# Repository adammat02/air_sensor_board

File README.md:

# Air Sensor Board

A low-power air sensor board (temperature and humidity) based on the Nordic **nRF54L15** SoC, designed to run as a **Matter** device.

The hardware is designed in KiCad.

## Features

- **MCU:** Nordic nRF54L15 (2.4 GHz radio, Thread / Bluetooth LE)
- **Sensor:** Sensirion SHT3x digital temperature and humidity sensor (I²C)
- **Status LED:** indicates device state (pairing, network connection, errors)
- **Button:** user input (e.g. commissioning, factory reset)
- **External flash memory:** extra storage, e.g. for OTA firmware updates (DFU)
- **Antenna:** 2.4 GHz PCB antenna
- **Power:** CR2032 coin cell battery
- **Battery monitoring:** battery voltage measured with the built-in SAADC
- **Clocks:** two external crystal oscillators
  - high-frequency crystal (HFXO, 32 MHz) for the radio and high-speed clock
  - low-frequency crystal (LFXO, 32.768 kHz) for low-power timekeeping in sleep modes

## Matter

The board is built to work in a **Matter** network, using **Thread** as the transport and **Bluetooth LE** for commissioning. It is meant to report temperature, humidity, and battery level to a Matter controller (e.g. Apple Home, Google Home, Home Assistant).

## Repository layout

| File | Description |
|------|-------------|
| `air_sensor_board.kicad_pro` | KiCad project |
| `air_sensor_board.kicad_sch` | Schematic |
| `air_sensor_board.kicad_pcb` | PCB layout |

## Tools

- [KiCad](https://www.kicad.org/) (hardware design)
- [nRF Connect SDK](https://www.nordicsemi.com/Products/Development-software/nRF-Connect-SDK) (firmware, Matter support)

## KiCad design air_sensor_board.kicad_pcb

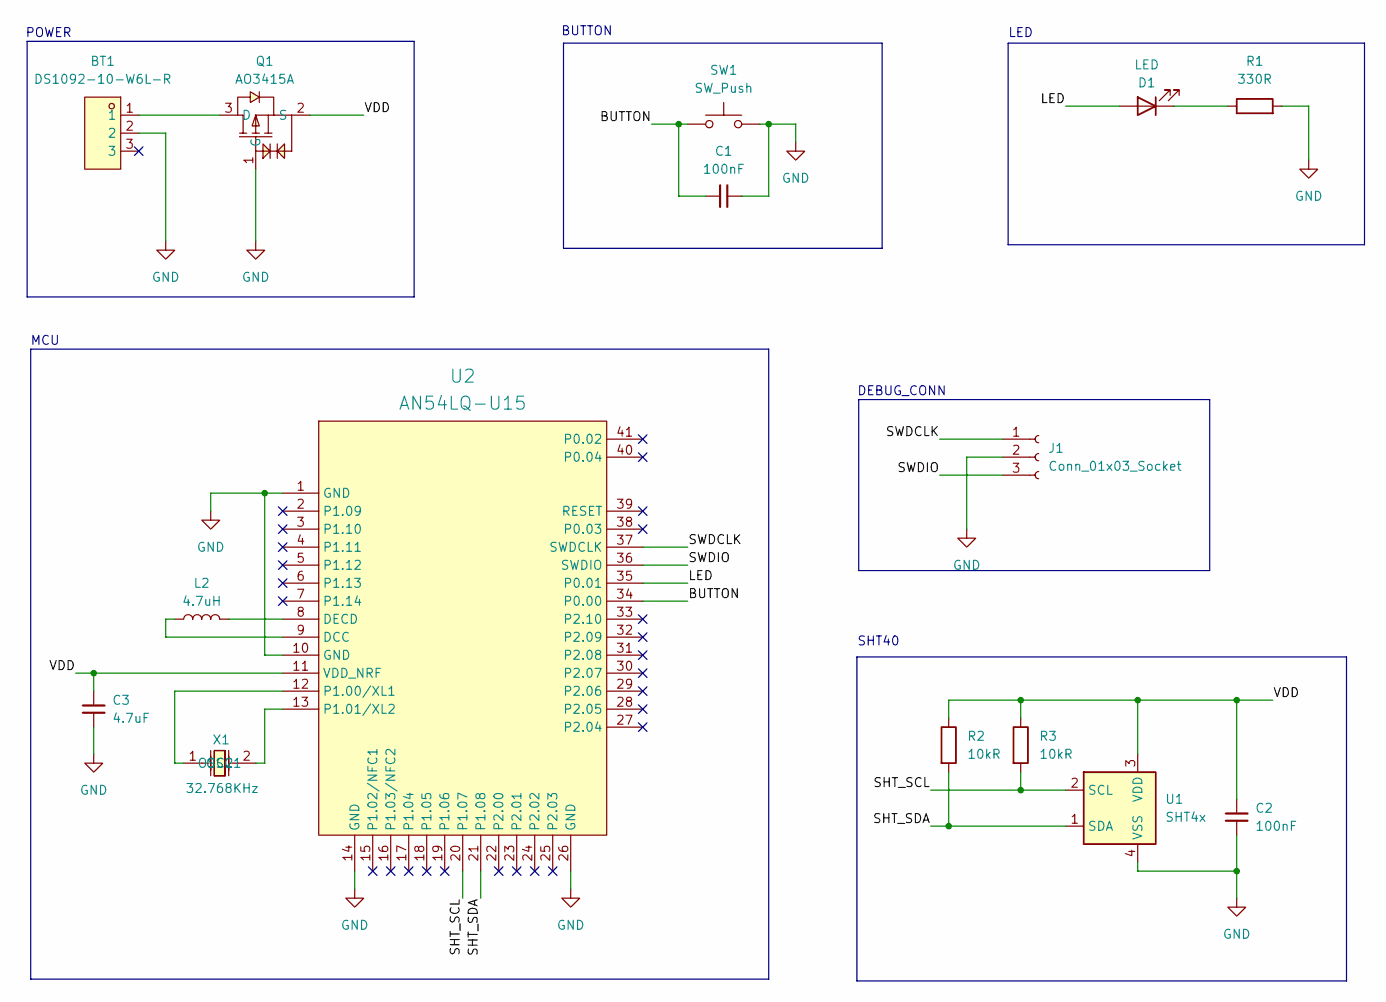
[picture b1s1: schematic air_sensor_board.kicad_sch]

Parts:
BT1: DS1092-10-W6L-R; BAT-SMD_79527141; MPN DS1092-10-W6L-R; LCSC Part C19944592
C1, C2: 100nF; C_0603_1608Metric
C3: 4.7uF; C_0603_1608Metric
D1: LED; LED_0805_2012Metric
J1: Conn_01x03_Socket; JST_SH_SM03B-SRSS-TB_1x03-1MP_P1.00mm_Horizontal
L2: 4.7uH; L_0603_1608Metric
Q1: AO3415A; SOT-23-3_L2.9-W1.6-P1.90-LS2.8-BR; MPN AO3415A; LCSC Part C133233
R1: 330R; R_0603_1608Metric
R2, R3: 10kR; R_0603_1608Metric
SW1: SW_Push; SW_SPST_PTS810
U1: SHT4x; Sensirion_DFN-4_1.5x1.5mm_P0.8mm_SHT4x_NoCentralPad
U2: AN54LQ-U15
X1: 32.768KHz; OSC-SMD_L3.2-W1.5; MPN ABS07-32.768KHZ-7-T; LCSC Part C276424

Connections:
/BUTTON: C1.1, SW1.1, U2.34 (P0.00)
/LED: D1.2 (A), U2.35 (P0.01)
/SHT_SCL: R3.2, U1.2 (SCL), U2.20 (P1.07)
/SHT_SDA: R2.2, U1.1 (SDA), U2.21 (P1.08)
/SWDCLK: J1.1, U2.37 (SWDCLK)
/SWDIO: J1.3, U2.36 (SWDIO)
/VDD: C2.1, C3.1, Q1.2 (S), R2.1, R3.1, U1.3 (VDD), U2.11 (VDD_NRF)
GND: BT1.2, C1.2, C2.2, C3.2, J1.2, Q1.1 (G), R1.2, SW1.2, U1.4 (VSS), U2.1 (GND), U2.10 (GND), U2.14 (GND), U2.26 (GND)
unnamed: D1.1 (K), R1.1
unnamed: BT1.1, Q1.3 (D)
unnamed: L2.1, U2.9 (DCC)
unnamed: L2.2, U2.8 (DECD)
unnamed: U2.12 (P1.00/XL1), X1.1 (OSC1)
unnamed: U2.13 (P1.01/XL2), X1.2 (OSC2)

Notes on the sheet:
BUTTON
SHT40
LED
MCU
DEBUG_CONN
POWER

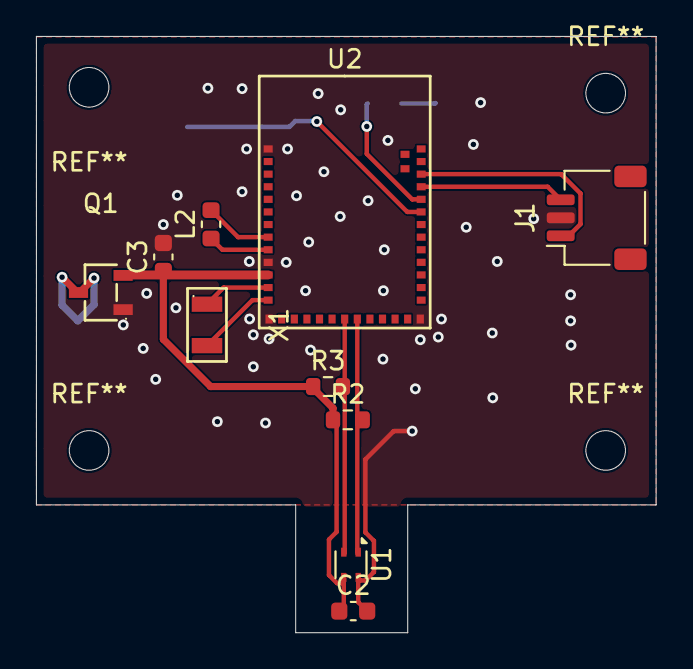
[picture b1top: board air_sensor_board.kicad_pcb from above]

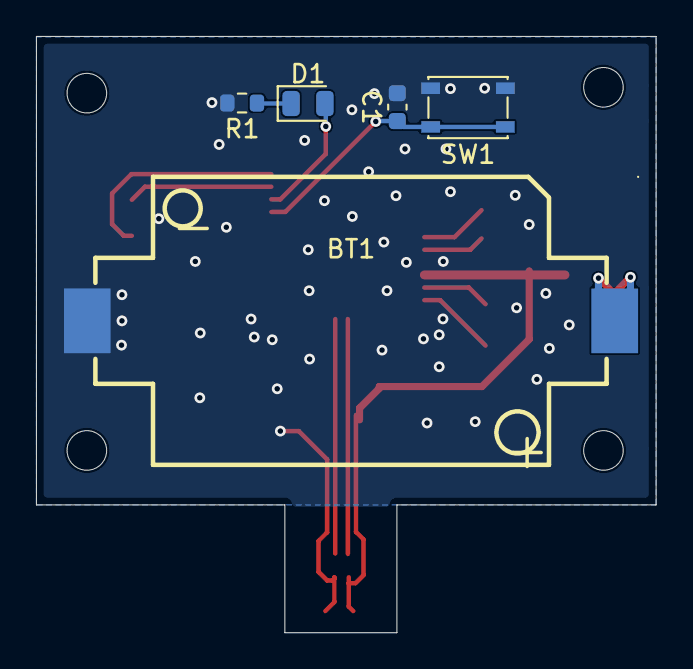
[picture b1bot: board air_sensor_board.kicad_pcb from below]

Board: 2 copper layers, 34.4 x 33.1 mm, 15 parts (5 on the bottom side), 14 nets.
